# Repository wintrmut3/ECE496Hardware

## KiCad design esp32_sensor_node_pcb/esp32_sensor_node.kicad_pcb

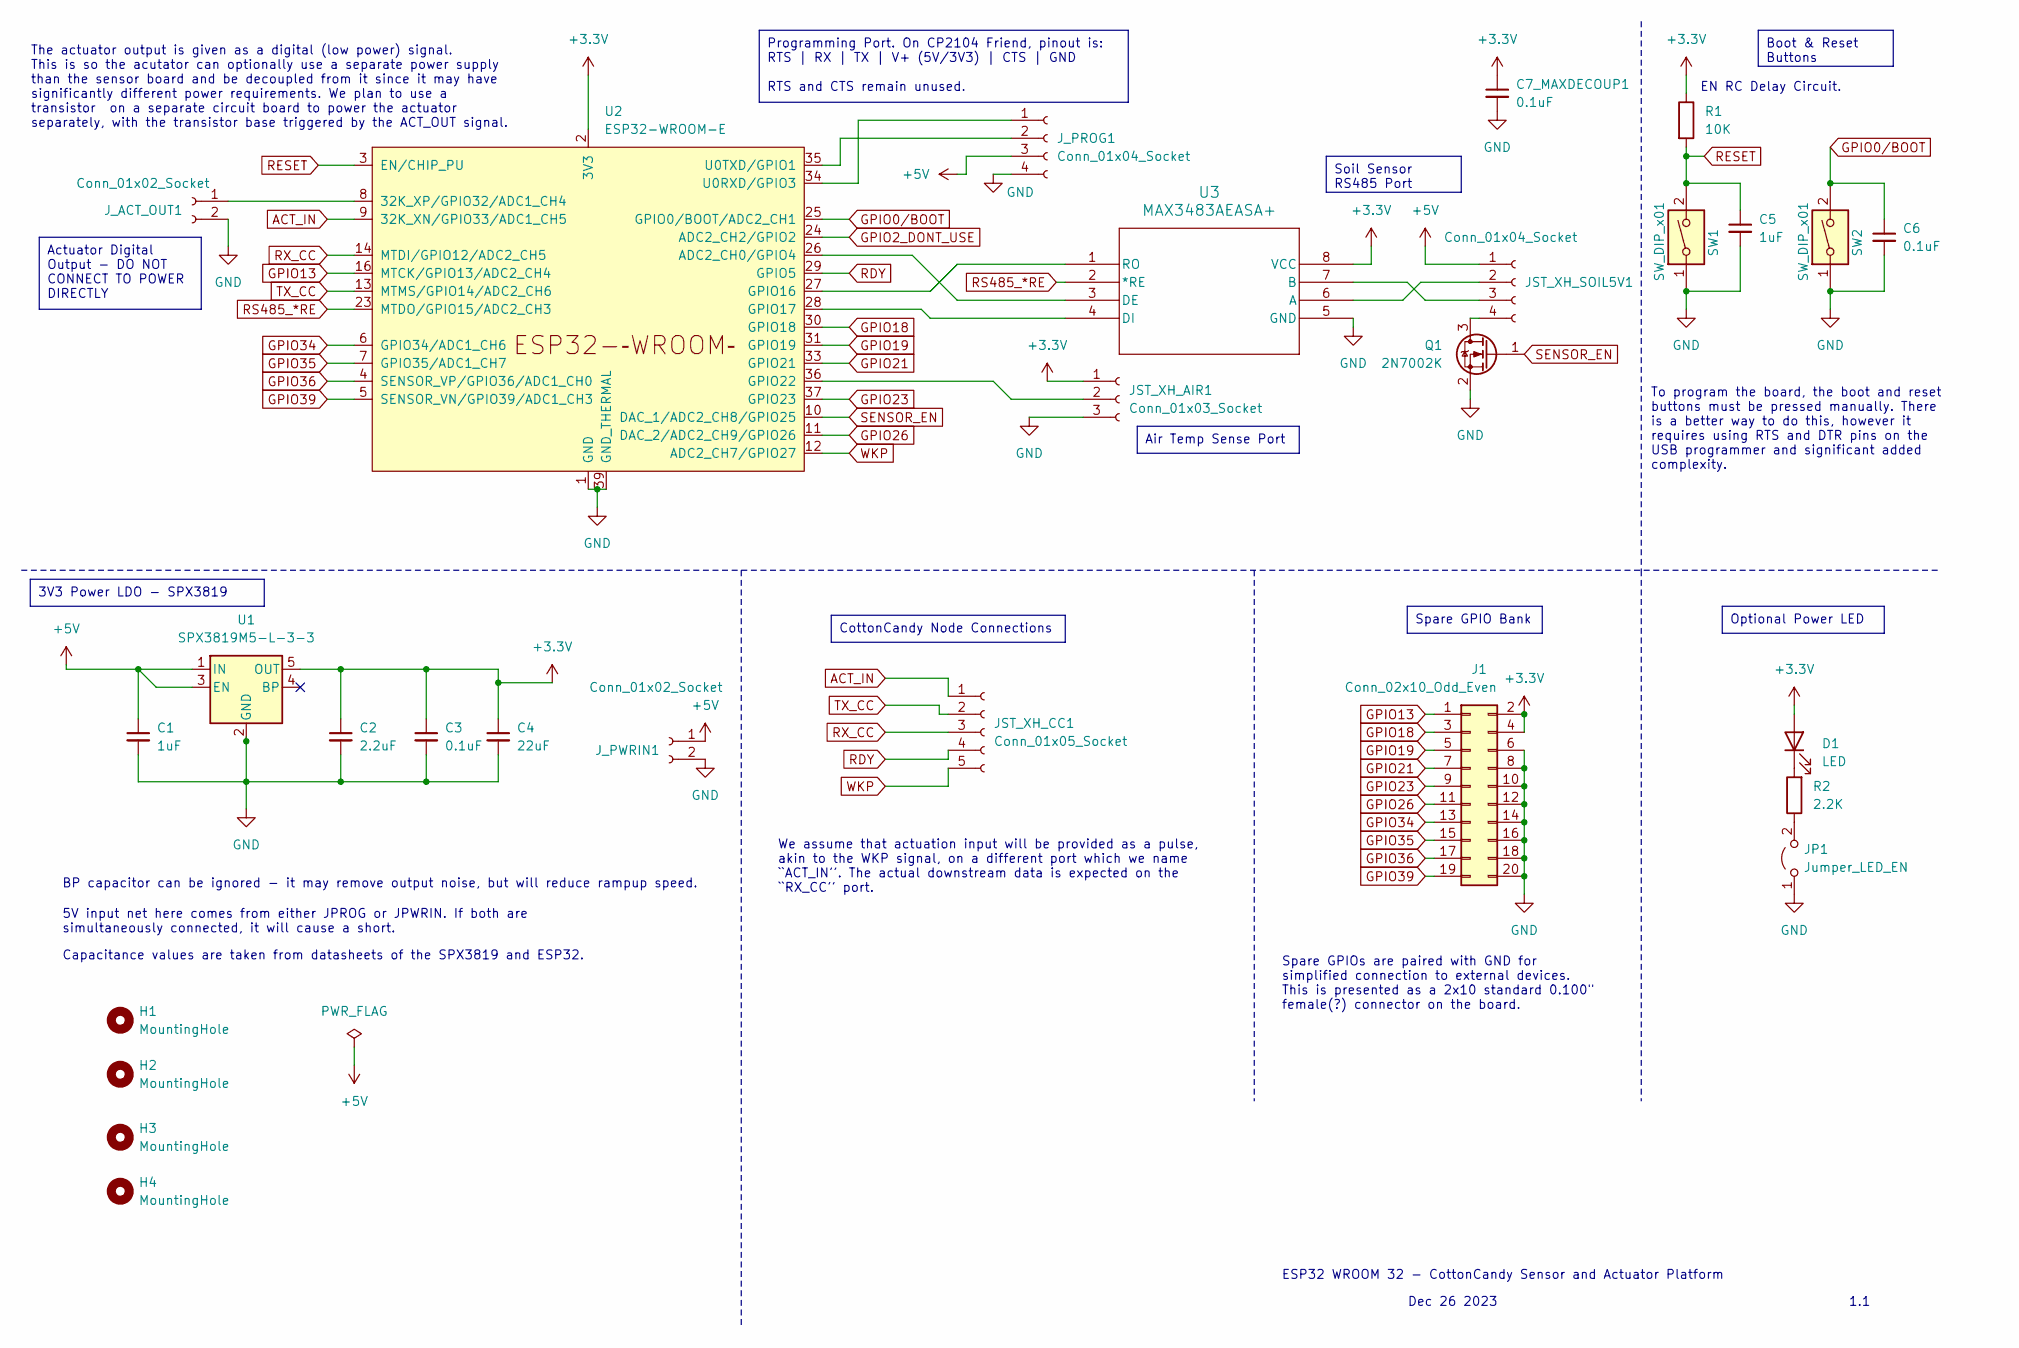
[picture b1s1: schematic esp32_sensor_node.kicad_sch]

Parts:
C1, C5: 1uF; C_0603_1608Metric
C2: 2.2uF; C_0805_2012Metric
C3, C6, C7_MAXDECOUP1: 0.1uF; C_0603_1608Metric
C4: 22uF; C_0805_2012Metric
D1: LED; LED_0603_1608Metric
H1, H2, H3, H4: MountingHole; MountingHole_3.2mm_M3
J1: Conn_02x10_Odd_Even; PinSocket_2x10_P2.54mm_Vertical
JP1: Jumper_LED_EN; PinHeader_1x02_P2.54mm_Vertical
JST_XH_AIR1: Conn_01x03_Socket; JST_XH_B3B-XH-A_1x03_P2.50mm_Vertical
JST_XH_CC1: Conn_01x05_Socket; JST_XH_B5B-XH-A_1x05_P2.50mm_Vertical
JST_XH_SOIL5V1: Conn_01x04_Socket; JST_XH_B4B-XH-A_1x04_P2.50mm_Vertical
J_ACT_OUT1: Conn_01x02_Socket; JST_XH_B2B-XH-A_1x02_P2.50mm_Vertical
J_PROG1: Conn_01x04_Socket; PinSocket_1x04_P2.54mm_Vertical
J_PWRIN1: Conn_01x02_Socket; JST_XH_B2B-XH-A_1x02_P2.50mm_Vertical
Q1: 2N7002K; SOT-23
R1: 10K; R_0603_1608Metric
R2: 2.2K; R_0603_1608Metric
SW1, SW2: SW_DIP_x01; SW_Tactile_SPST_NO_Straight_CK_PTS636Sx25SMTRLFS
U1: SPX3819M5-L-3-3; SOT-23-5
U2: ESP32-WROOM-E; ESP32-WROOM-32E
U3: MAX3483AEASA+; 21-0041B_8_MXM

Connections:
+3.3V: C2.1, C3.1, C4.1, C7_MAXDECOUP1.1, D1.2 (A), J1.2, J1.4, JST_XH_AIR1.1, R1.1, U1.5 (OUT), U2.2 (3V3), U3.8 (VCC)
+5V: C1.1, JST_XH_SOIL5V1.1, J_PROG1.3, J_PWRIN1.1, U1.1 (IN), U1.3 (EN)
ACT_IN: JST_XH_CC1.1, U2.9 (32K_XN/GPIO33/ADC1_CH5)
GND: C1.2, C2.2, C3.2, C4.2, C5.2, C6.2, C7_MAXDECOUP1.2, J1.6, J1.8, J1.10, J1.12, J1.14, J1.16, J1.18, J1.20, JP1.1 (A), JST_XH_AIR1.3, J_ACT_OUT1.2, J_PROG1.4, J_PWRIN1.2, Q1.2 (S), SW1.1, SW2.1, U1.2 (GND), U2.1 (GND), U2.15 (GND), U2.38 (GND), U2.39 (GND_THERMAL), U3.5 (GND)
GPIO0/BOOT: C6.1, SW2.2, U2.25 (GPIO0/BOOT/ADC2_CH1)
GPIO2_DONT_USE: U2.24 (ADC2_CH2/GPIO2)
GPIO13: J1.1, U2.16 (MTCK/GPIO13/ADC2_CH4)
GPIO18: J1.3, U2.30 (GPIO18)
GPIO19: J1.5, U2.31 (GPIO19)
GPIO21: J1.7, U2.33 (GPIO21)
GPIO23: J1.9, U2.37 (GPIO23)
GPIO26: J1.11, U2.11 (DAC_2/ADC2_CH9/GPIO26)
GPIO34: J1.13, U2.6 (GPIO34/ADC1_CH6)
GPIO35: J1.15, U2.7 (GPIO35/ADC1_CH7)
GPIO36: J1.17, U2.4 (SENSOR_VP/GPIO36/ADC1_CH0)
GPIO39: J1.19, U2.5 (SENSOR_VN/GPIO39/ADC1_CH3)
unnamed: D1.1 (K), R2.2
unnamed: JP1.2 (B), R2.1
unnamed: JST_XH_AIR1.2, U2.36 (GPIO22)
unnamed: JST_XH_SOIL5V1.2, U3.6 (A)
unnamed: JST_XH_SOIL5V1.3, U3.7 (B)
unnamed: JST_XH_SOIL5V1.4, Q1.3 (D)
unnamed: J_ACT_OUT1.1, U2.8 (32K_XP/GPIO32/ADC1_CH4)
unnamed: J_PROG1.1, U2.34 (U0RXD/GPIO3)
unnamed: J_PROG1.2, U2.35 (U0TXD/GPIO1)
unnamed: U2.26 (ADC2_CH0/GPIO4), U3.3 (DE)
unnamed: U2.27 (GPIO16), U3.1 (RO)
unnamed: U2.28 (GPIO17), U3.4 (DI)
RDY: JST_XH_CC1.4, U2.29 (GPIO5)
RESET: C5.1, R1.2, SW1.2, U2.3 (EN/CHIP_PU)
RS485_*RE: U2.23 (MTDO/GPIO15/ADC2_CH3), U3.2 (*RE)
RX_CC: JST_XH_CC1.3, U2.14 (MTDI/GPIO12/ADC2_CH5)
SENSOR_EN: Q1.1 (G), U2.10 (DAC_1/ADC2_CH8/GPIO25)
TX_CC: JST_XH_CC1.2, U2.13 (MTMS/GPIO14/ADC2_CH6)
WKP: JST_XH_CC1.5, U2.12 (ADC2_CH7/GPIO27)

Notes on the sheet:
Boot & Reset Buttons
3V3 Power LDO - SPX3819
Optional Power LED
Programming Port. On CP2104 Friend, pinout is: RTS | RX | TX | V+ (5V/3V3) | CTS | GND RTS and CTS remain unused.
Air Temp Sense Port
Soil Sensor RS485 Port
Actuator Digital Output - DO NOT CONNECT TO POWER DIRECTLY
CottonCandy Node Connections
Spare GPIO Bank
We assume that actuation input will be provided as a pulse, akin to the WKP signal, on a different port which we name ``ACT_IN''. The actual downstream data is expected on the ``RX_CC'' port.
To program the board, the boot and reset buttons must be pressed manually. There is a better way to do this, however it requires using RTS and DTR pins on the USB programmer and significant added complexity.
Capacitance values are taken from datasheets of the SPX3819 and ESP32.
BP capacitor can be ignored - it may remove output noise, but will reduce rampup speed.
Dec 26 2023
Spare GPIOs are paired with GND for simplified connection to external devices. This is presented as a 2x10 standard 0.100" female(?) connector on the board.
EN RC Delay Circuit.
1.1
ESP32 WROOM 32 - CottonCandy Sensor and Actuator Platform
5V input net here comes from either JPROG or JPWRIN. If both are simultaneously connected, it will cause a short.
The actuator output is given as a digital (low power) signal. This is so the acutator can optionally use a separate power supply than the sensor board and be decoupled from it since it may have significantly different power requirements. We plan to use a transistor on a separate circuit board to po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

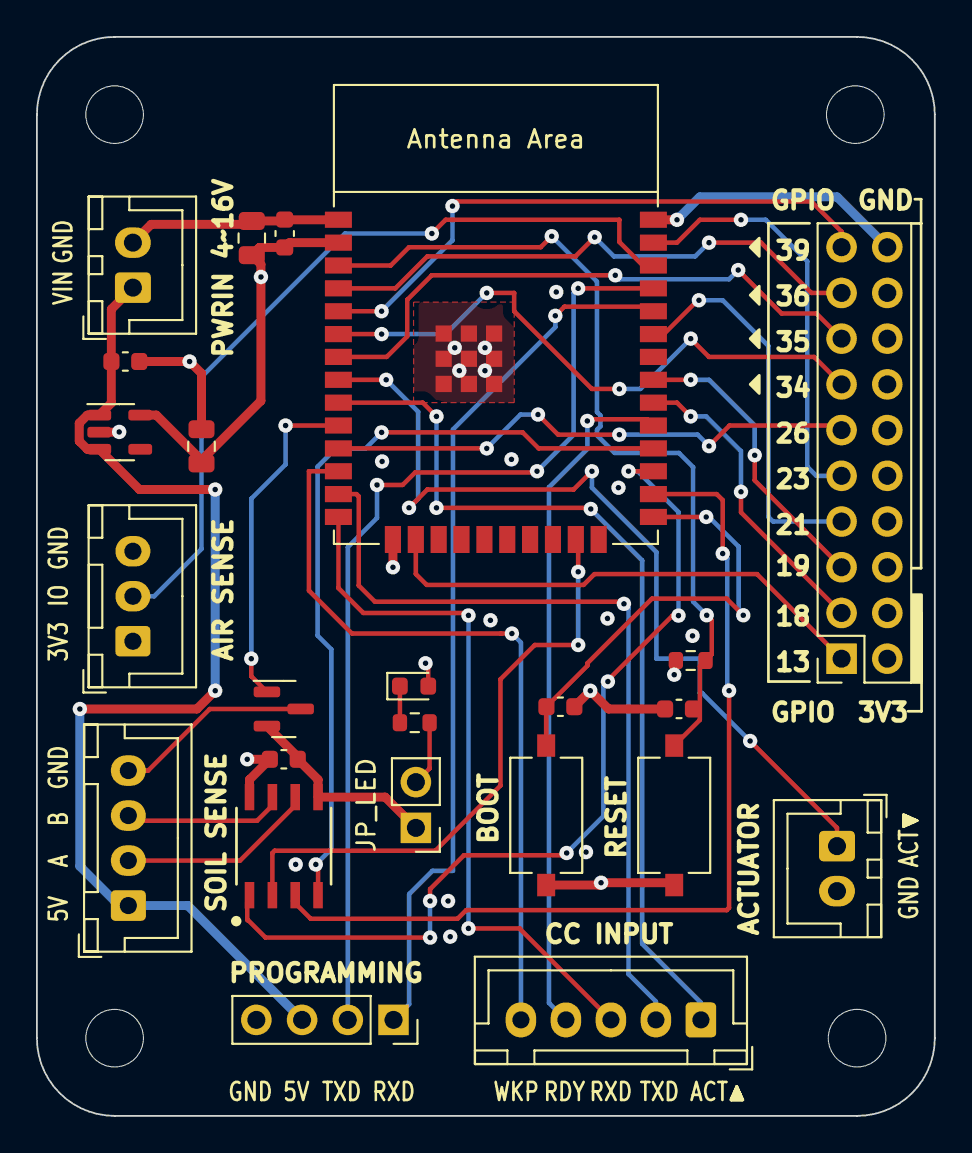
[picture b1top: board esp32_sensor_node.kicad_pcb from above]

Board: 4 copper layers, 49.9 x 59.9 mm, 28 parts (0 on the bottom side), 34 nets.

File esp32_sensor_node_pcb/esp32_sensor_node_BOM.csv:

Comment,Designator,Footprint,LCSC
"1uF","C1,C5","Capacitor_SMD:C_0603_1608Metric",""
"2.2uF","C2","Capacitor_SMD:C_0603_1608Metric",""
"0.1uF","C3,C6,C7_MAXDECOUP1","Capacitor_SMD:C_0603_1608Metric",""
"22uF","C4","Capacitor_SMD:C_0805_2012Metric",""
"LED","D1","LED_SMD:LED_0603_1608Metric",""
"MountingHole","H1,H2,H3,H4","MountingHole:MountingHole_3.2mm_M3",""
"Conn_02x10_Odd_Even","J1","Connector_PinSocket_2.54mm:PinSocket_2x10_P2.54mm_Vertical",""
"Jumper_LED_EN","JP1","Connector_PinHeader_2.54mm:PinHeader_1x02_P2.54mm_Vertical",""
"Conn_01x03_Socket","JST_XH_AIR1","Connector_JST:JST_XH_B3B-XH-A_1x03_P2.50mm_Vertical",""
"Conn_01x05_Socket","JST_XH_CC1","Connector_JST:JST_XH_B5B-XH-A_1x05_P2.50mm_Vertical",""
"Conn_01x04_Socket","J_PROG1,JST_XH_SOIL5V1","Connector_JST:JST_XH_B4B-XH-A_1x04_P2.50mm_Vertical",""
"Conn_01x02_Socket","J_ACT_OUT1,J_PWRIN1","Connector_JST:JST_XH_B2B-XH-A_1x02_P2.50mm_Vertical",""
"2N7002K","Q1","Package_TO_SOT_SMD:SOT-23",""
"10K","R1","Resistor_SMD:R_0603_1608Metric",""
"2.2K","R2","Resistor_SMD:R_0603_1608Metric",""
"SW_DIP_x01","SW1,SW2","Button_Switch_SMD:SW_Tactile_SPST_NO_Straight_CK_PTS636Sx25SMTRLFS",""
"SPX3819M5-L-3-3","U1","Package_TO_SOT_SMD:SOT-23-5",""
"ESP32-WROOM-E","U2","PCM_Espressif:ESP32-WROOM-32E",""
"MAX3483AEASA+","U3","MAX3483:21-0041B_8_MXM",""

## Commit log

2023-12-03 Initial Push
2023-12-03 Add remote BOM
2023-12-03 ESP32 code
2023-12-03 Update BOM.csv
    Add disclaimer to BOM for missing inconsequential components. These can be viewed on the PCB source.
2023-12-03 Update BOM.csv
    Replace .100" with 100 mil to allow pretty printing
2023-12-03 Update BOM.csv
    Remove excess commas for pretty printing
2023-12-17 Changed power symbols, added 0.1uF decoupling cap, changed LED resistor value to 1.91k as per part availability on JLPCB.
2023-12-17 Updated schematic
2023-12-17 Added big 0805 22u capacitor, fixed reset capacitor, add capacitor for max ic decoupling
2023-12-17 Add mounting holes
2023-12-18 Setup initial board layout
2023-12-18 Complete first draft routing
2023-12-19 Add printouts
2023-12-24 Changed schematic - 3.3V to RS485, 5V to Soil sensor. Changed resistor from 1.9k to 4.7k. Finished routing of PCB with new schematic
2023-12-26 Add transfer vias for all HSS, remove some routing voids, standardize track lengths for power and signal
2023-12-26 Center MCU, reroute cleanup, add labels and shift components to fit
2023-12-26 Added constraints to board setup according to JLCPCB specifications for DRC checker. Arranged some text on silkscreen and some routing.
2023-12-26 Add 3v3 outputs on header. Shift labels for alignment. Add board names on back.
2023-12-27 Change LDO HT7833 -> SPX3819, reroute, relabel. Generate BOM testing.
2023-12-27 Changed 2.2uF cap to 0805. Added power flag on 5V and not-connected for BP pin. Changed all vias to 0.3mm hole size. Changed programming interface to 2.54mm PIN headers.
2023-12-27 Removed reference designators on the silk screen
2023-12-28 Add copyright & transfer vias. Checked ERC and DRC.
2023-12-28 Add fab files. Add dot next to MAX3843 to indicate pin1
2024-01-17 - Add delays to RS485 and correct pullup direction on transistor (still need to add capacitance to ~RE) - Add digitalwrite + delay instead of input pullup on DE due to possible board fault (Input pul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
2024-01-29 Updated ESP32 code with pH + NPK readings
2024-02-01 Adding CAD
2024-02-07 ESP32 with Intent working
2024-02-12 Added OLED prototyping code
2024-02-17 ESP32 code with intent not working
2024-02-24 Pump + intent + pH readings

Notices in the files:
esp32_sensor_node_pcb/esp32_sensor_node.kicad_pcb:
Copyright © 2023 UofT Network Research Lab
